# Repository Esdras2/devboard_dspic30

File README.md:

# devboard_dspic30
dspic devboard for edu purpose

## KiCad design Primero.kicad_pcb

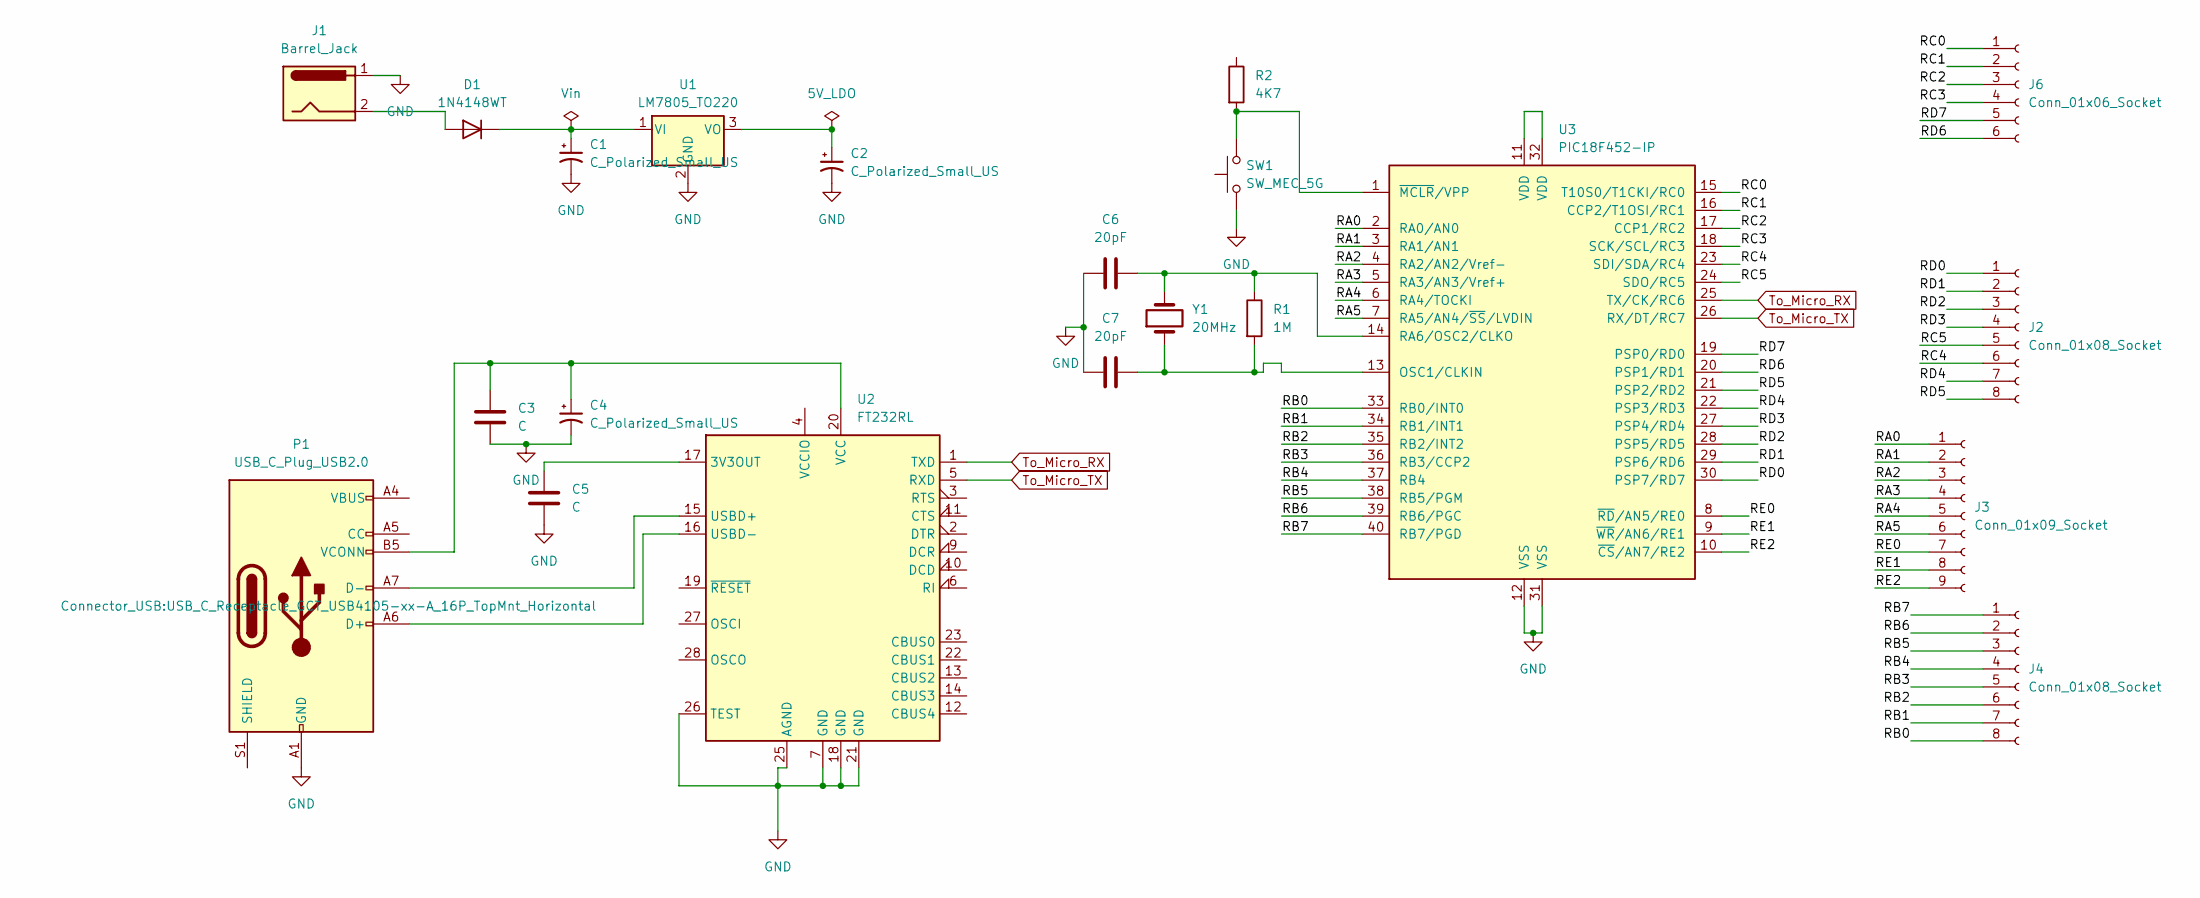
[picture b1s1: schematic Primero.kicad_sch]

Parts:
C1, C2: C_Polarized_Small_US; CP_Elec_4x3.9
C3, C5: C; C_0201_0603Metric
C4: C_Polarized_Small_US; CP_Elec_3x5.3
C6, C7: 20pF; C_0201_0603Metric
D1: 1N4148WT; D_SOD-523
J1: Barrel_Jack; BarrelJack_CUI_PJ-063AH_Horizontal
J2, J4: Conn_01x08_Socket; Hirose_DF13-08P-1.25DSA_1x08_P1.25mm_Vertical
J3: Conn_01x09_Socket; Hirose_DF13-09P-1.25DSA_1x09_P1.25mm_Vertical
J6: Conn_01x06_Socket; Hirose_DF13-06P-1.25DSA_1x06_P1.25mm_Vertical
P1: USB_C_Plug_USB2.0; USB_C_Receptacle_GCT_USB4105-xx-A_16P_TopMnt_Horizontal
R1: 1M; R_0201_0603Metric
R2: 4K7; R_0201_0603Metric
SW1: SW_MEC_5G; SW_Push_1P1T_XKB_TS-1187A
U1: LM7805_TO220; TO-220-3_Vertical
U2: FT232RL; SSOP-28_5.3x10.2mm_P0.65mm
U3: PIC18F452-IP; DIP-40_W15.24mm
Y1: 20MHz; Crystal_HC52-U_Vertical

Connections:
/RA0: J3.1, U3.2 (RA0/AN0)
/RA1: J3.2, U3.3 (RA1/AN1)
/RA2: J3.3, U3.4 (RA2/AN2/Vref-)
/RA3: J3.4, U3.5 (RA3/AN3/Vref+)
/RA4: J3.5, U3.6 (RA4/TOCKI)
/RA5: J3.6, U3.7 (RA5/AN4/~SS/LVDIN)
/RB0: J4.8, U3.33 (RB0/INT0)
/RB1: J4.7, U3.34 (RB1/INT1)
/RB2: J4.6, U3.35 (RB2/INT2)
/RB3: J4.5, U3.36 (RB3/CCP2)
/RB4: J4.4, U3.37 (RB4)
/RB5: J4.3, U3.38 (RB5/PGM)
/RB6: J4.2, U3.39 (RB6/PGC)
/RB7: J4.1, U3.40 (RB7/PGD)
/RC0: J6.1, U3.15 (T10S0/T1CKI/RC0)
/RC1: J6.2, U3.16 (CCP2/T1OSI/RC1)
/RC2: J6.3, U3.17 (CCP1/RC2)
/RC3: J6.4, U3.18 (SCK/SCL/RC3)
/RC4: J2.6, U3.23 (SDI/SDA/RC4)
/RC5: J2.5, U3.24 (SDO/RC5)
/RD0: J2.1, U3.30 (PSP7/RD7)
/RD1: J2.2, U3.29 (PSP6/RD6)
/RD2: J2.3, U3.28 (PSP5/RD5)
/RD3: J2.4, U3.27 (PSP4/RD4)
/RD4: J2.7, U3.22 (PSP3/RD3)
/RD5: J2.8, U3.21 (PSP2/RD2)
/RD6: J6.6, U3.20 (PSP1/RD1)
/RD7: J6.5, U3.19 (PSP0/RD0)
/RE0: J3.7, U3.8 (~RD/AN5/RE0)
/RE1: J3.8, U3.9 (~WR/AN6/RE1)
/RE2: J3.9, U3.10 (~CS/AN7/RE2)
GND: C1.2, C2.2, C3.2, C4.2, C5.2, C6.1, C7.1, J1.1, P1.A1 (GND), P1.A12 (GND), P1.B1 (GND), P1.B12 (GND), SW1.1 (A), SW1.2 (A), U1.2 (GND), U2.7 (GND), U2.18 (GND), U2.21 (GND), U2.25 (AGND), U2.26 (TEST), U3.12 (VSS), U3.31 (VSS)
unnamed: D1.2 (A), J1.2
unnamed: C1.1, D1.1 (K), U1.1 (VI)
unnamed: P1.A6 (D+), U2.16 (USBD-)
unnamed: P1.A7 (D-), U2.15 (USBD+)
unnamed: P1.A4 (VBUS), P1.A9 (VBUS), P1.B4 (VBUS), P1.B9 (VBUS)
unnamed: C3.1, C4.1, P1.B5 (VCONN), U2.20 (VCC)
unnamed: C2.1, U1.3 (VO)
unnamed: C5.1, U2.17 (3V3OUT)
unnamed: C7.2, R1.2, U3.13 (OSC1/CLKIN), Y1.1
unnamed: C6.2, R1.1, U3.14 (RA6/OSC2/CLKO), Y1.2
unnamed: U3.11 (VDD), U3.32 (VDD)
unnamed: R2.2, SW1.3 (B), SW1.4 (B), U3.1 (~MCLR/VPP)
To_Micro_RX: U2.1 (TXD), U3.25 (TX/CK/RC6)
To_Micro_TX: U2.5 (RXD), U3.26 (RX/DT/RC7)

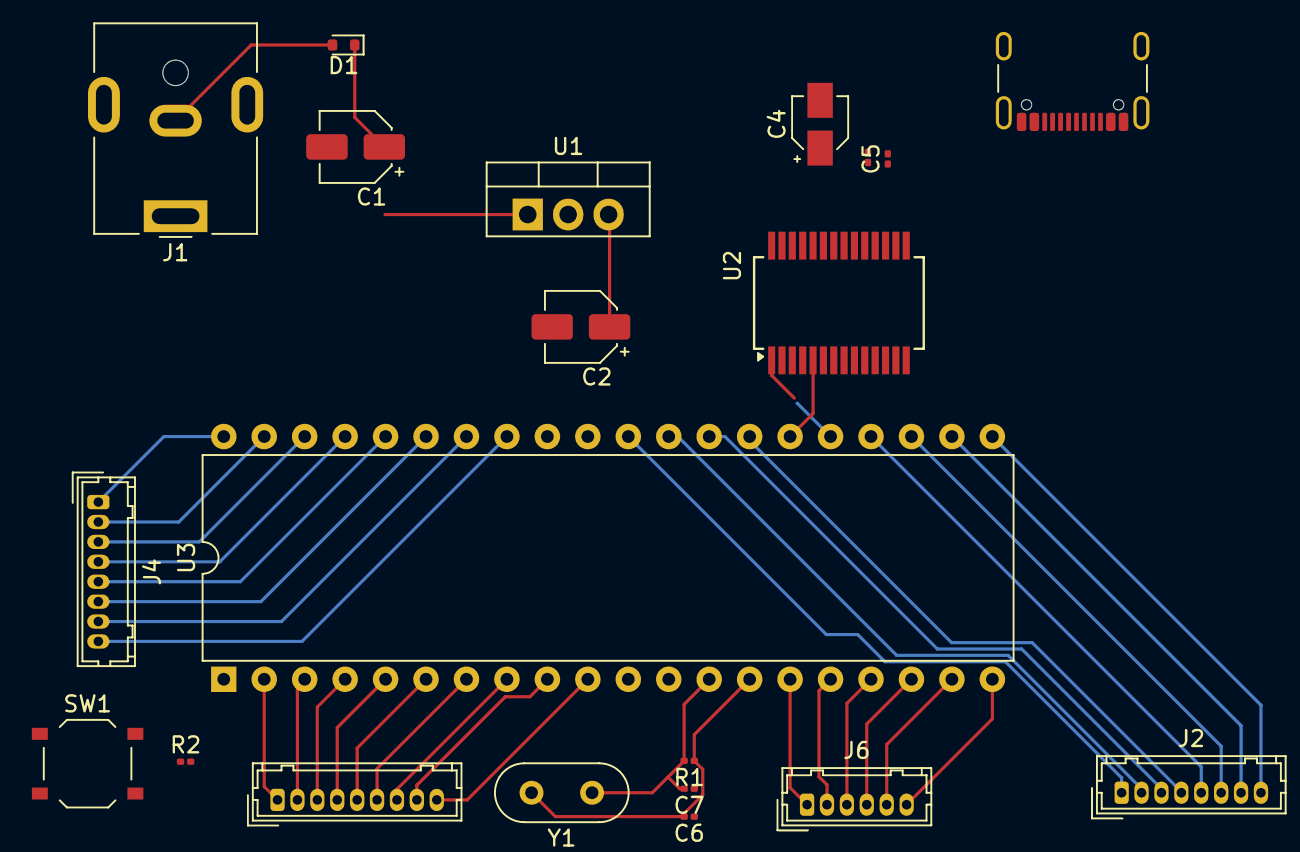
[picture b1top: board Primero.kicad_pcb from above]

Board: 2 copper layers, 21 parts (0 on the bottom side), 46 nets.

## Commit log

2025-02-14 initial files
2025-02-14 modify gitignore
2025-02-14 push to repository
